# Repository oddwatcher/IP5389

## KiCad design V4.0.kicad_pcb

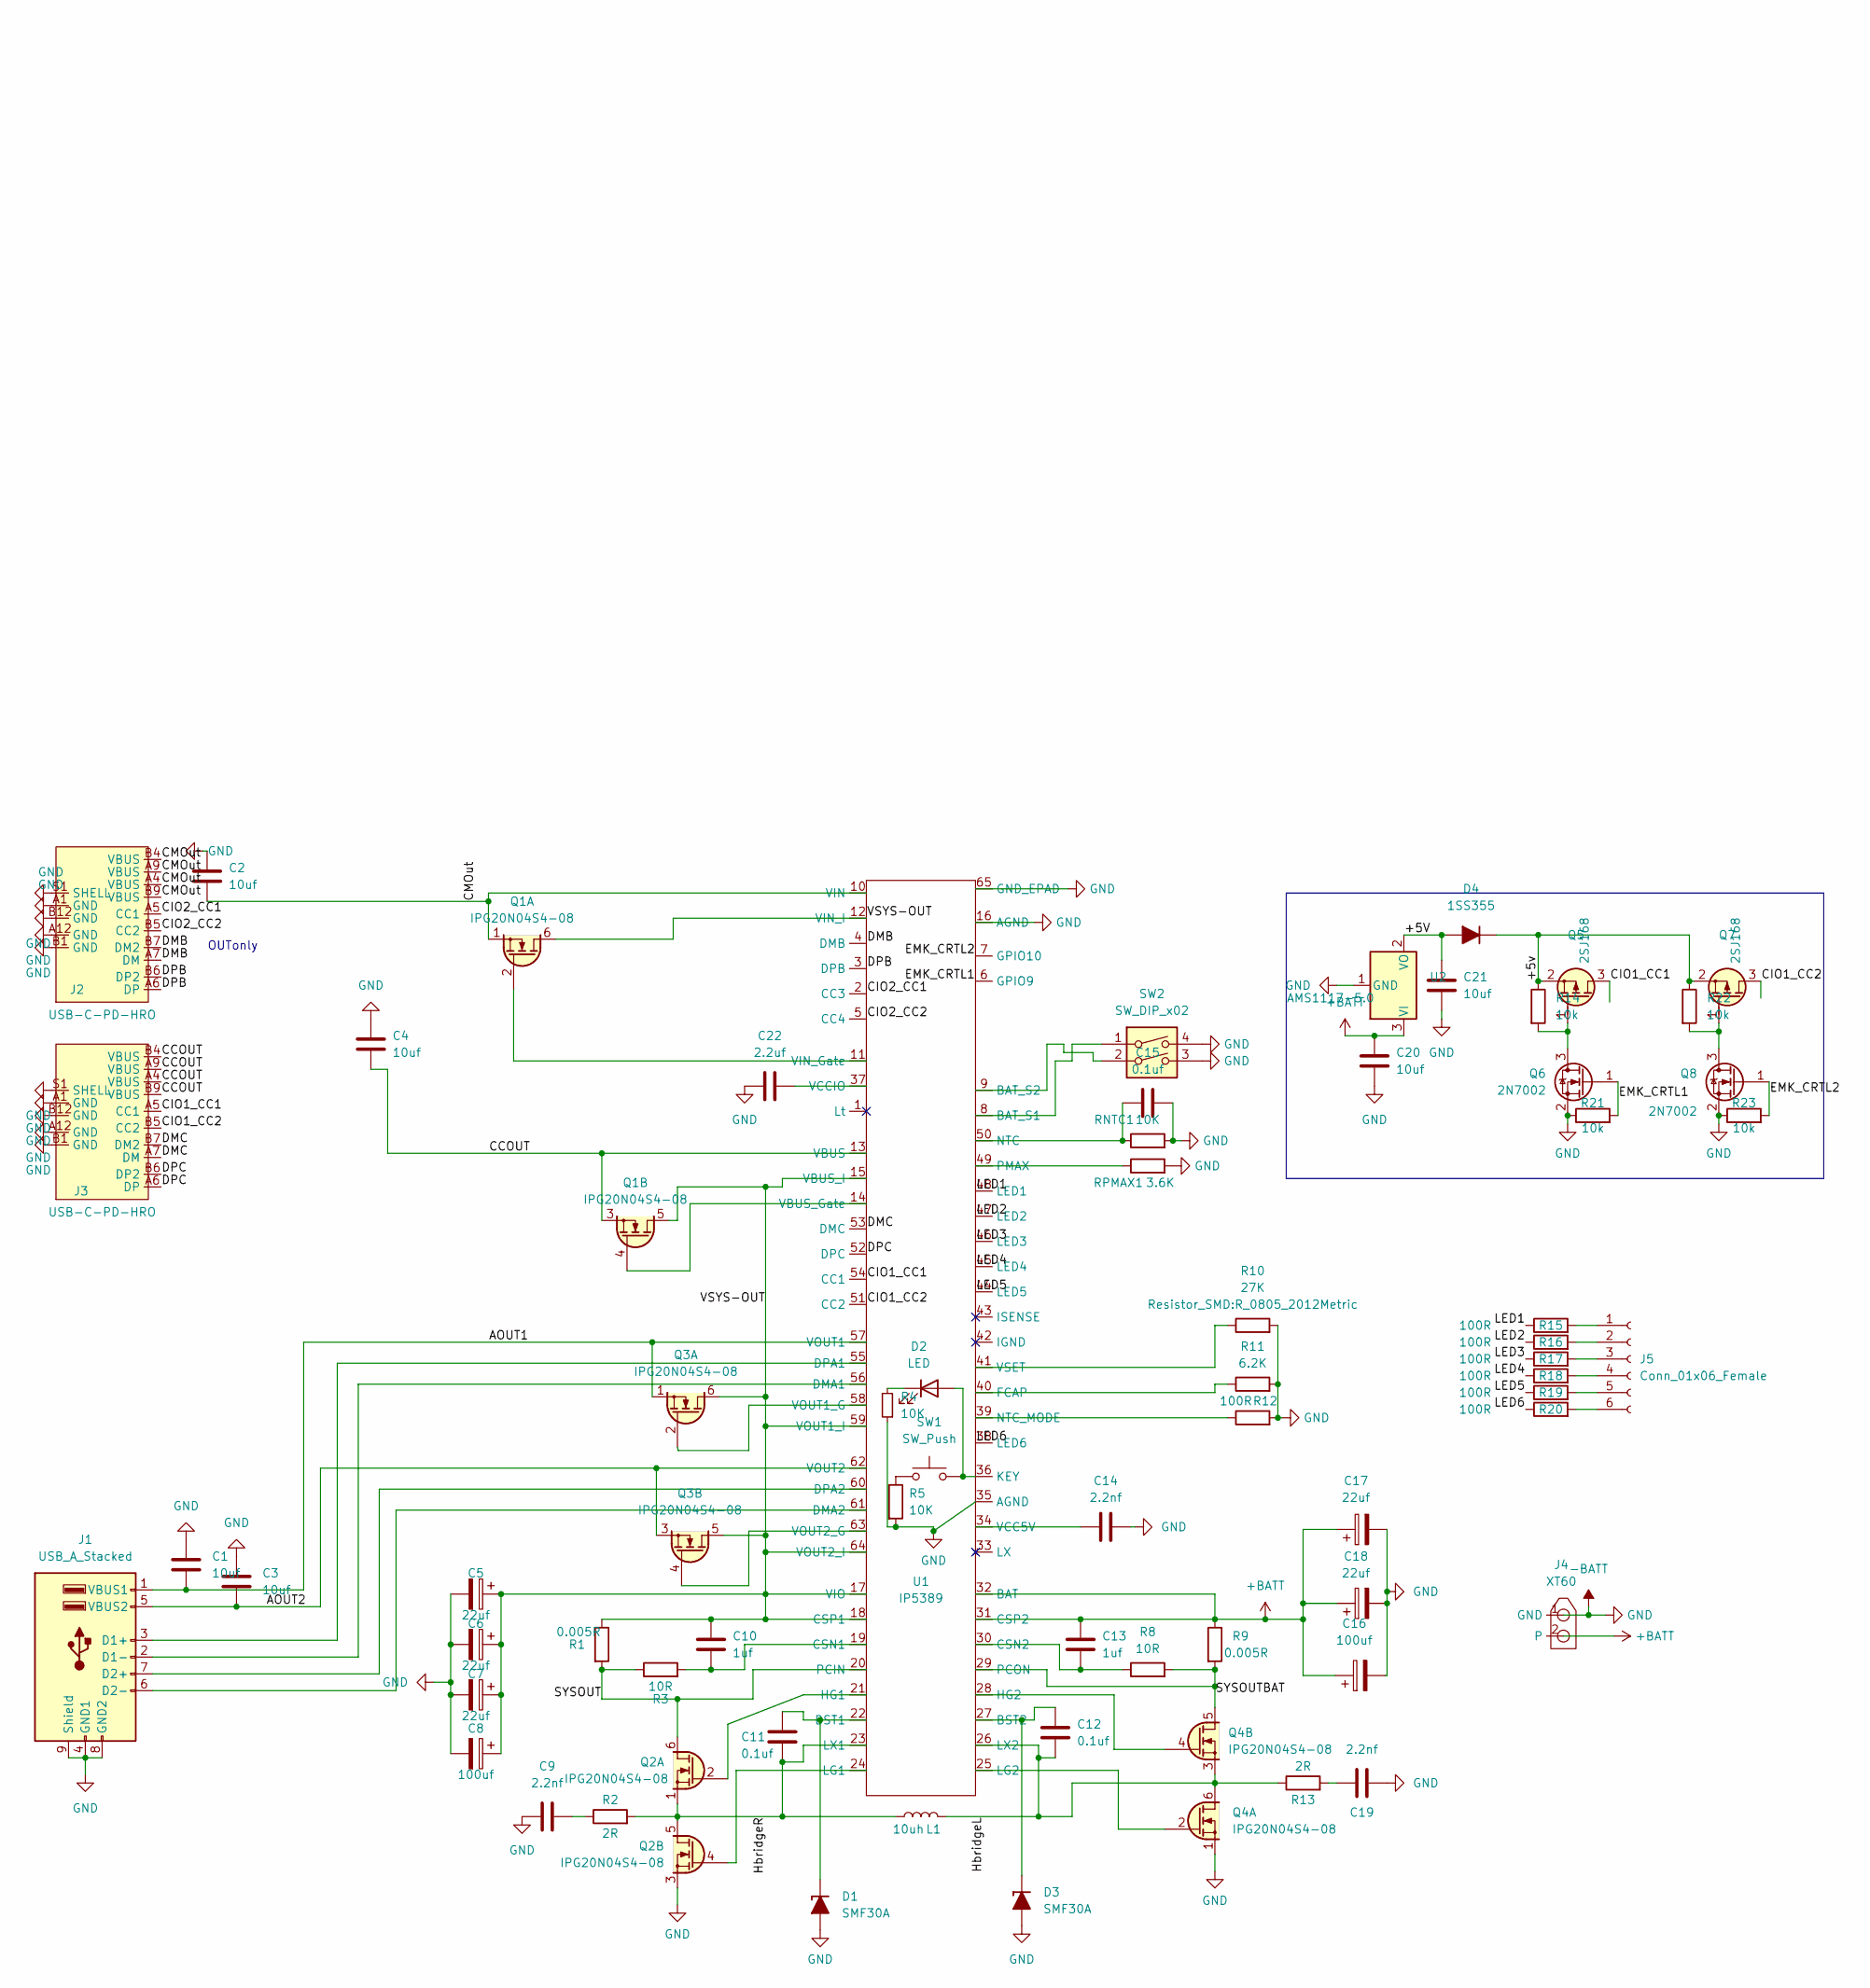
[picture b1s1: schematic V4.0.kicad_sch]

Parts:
C1, C2, C3, C4: 10uf; CP_EIA-7343-31_Kemet-D
C5, C6, C7, C17, C18: 22uf; C_1206_3216Metric
C8, C16: 100uf; CP_EIA-7343-31_Kemet-D
C9, C14, C19: 2.2nf; C_0805_2012Metric
C10, C13: 1uf; C_0805_2012Metric
C11, C12, C15: 0.1uf; C_0805_2012Metric
C20, C21: 10uf; C_0805_2012Metric
C22: 2.2uf; C_0805_2012Metric
D1, D3: SMF30A; D_SOD-123F
D2: LED; C_0805_2012Metric
D4: 1SS355; D_SOD-323
J1: USB_A_Stacked; USB_A_Wuerth_61400826021_Horizontal_Stacked
J2, J3: USB-C-PD-HRO; USB_C_Receptacle_HRO_TYPE-C-31-M-12
J4: XT60; AMASS_XT30U-M_1x02_P5.0mm_Vertical
J5: Conn_01x06_Female; PinHeader_1x06_P2.54mm_Vertical
L1: 10uh; L_12x12mm_H6mm
Q1, Q2, Q3, Q4: IPG20N04S4-08; Infineon_PG-TDSON-8_Dual
Q5, Q7: 2SJ168; SC-59
Q6, Q8: 2N7002; SOT-23
R1, R9: 0.005R; R_1206_3216Metric
R2, R13: 2R; R_1206_3216Metric
R3, R8: 10R; R_0805_2012Metric
R4, R5: 10K; R_0805_2012Metric
R10: 27K; R_0805_2012Metric
R11: 6.2K; R_0805_2012Metric
R12, R15, R16, R17, R18, R19, R20: 100R; R_0805_2012Metric
R14, R21, R22, R23: 10k; R_0805_2012Metric
RNTC1: 10K; R_0805_2012Metric
RPMAX1: 3.6K; R_0805_2012Metric
SW1: SW_Push; SW_Push_1P1T_NO_CK_KMR2
SW2: SW_DIP_x02; SW_DIP_SPSTx02_Slide_6.7x6.64mm_W7.62mm_P2.54mm_LowProfile
U1: IP5389; QFN-64-1EP_8x8mm_P0.4mm_EP6.5x6.5mm_ThermalVias
U2: AMS1117-5.0; SOT-223

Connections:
+BATT: C13.1, C16.1, C17.1, C18.1, C20.1, J4.2, R9.1, U1.31 (CSP2), U1.32 (BAT), U2.3 (VI)
-BATT: C1.1, C2.1, C3.1, C4.1, C5.2, C6.2, C7.2, C8.2, C9.1, C14.2, C15.1, C16.2, C17.2, C18.2, C19.1, C20.2, C21.2, C22.1, D1.2 (A), D3.2 (A), J1.4 (GND1), J1.8 (GND2), J1.9 (Shield), J2.A1 (GND), J2.A12 (GND), J2.B1 (GND), J2.B12 (GND), J2.S1 (SHELL), J3.A1 (GND), J3.A12 (GND), J3.B1 (GND), J3.B12 (GND), J3.S1 (SHELL), J4.1 (GND), Q2.3 (S2), Q4.1 (S1), Q6.2 (S), Q8.2 (S), R4.1, R5.2, R10.2, R11.2, R12.2, R21.1, R23.1, RNTC1.2, RPMAX1.2, SW2.3, SW2.4, U1.16 (AGND), U1.35 (AGND), U1.65 (GND_EPAD), U2.1 (GND)
/+5V: C21.1, D4.2 (A), U2.2 (VO)
/+5v: D4.1 (K), Q5.2 (S), Q7.2 (S), R14.1, R22.1
/AOUT1: C1.2, J1.1 (VBUS1), Q3.1 (S1), U1.57 (VOUT1)
/AOUT2: C3.2, J1.5 (VBUS2), Q3.3 (S2), U1.62 (VOUT2)
/CCOUT: C4.2, J3.A4 (VBUS), J3.A9 (VBUS), J3.B4 (VBUS), J3.B9 (VBUS), Q1.3 (S2), U1.13 (VBUS)
/CIO1_CC1: J3.A5 (CC1), Q5.3 (D), U1.54 (CC1)
/CIO1_CC2: J3.B5 (CC2), Q7.3 (D), U1.51 (CC2)
/CIO2_CC1: J2.A5 (CC1), U1.2 (CC3)
/CIO2_CC2: J2.B5 (CC2), U1.5 (CC4)
/CMOut: C2.2, J2.A4 (VBUS), J2.A9 (VBUS), J2.B4 (VBUS), J2.B9 (VBUS), Q1.1 (S1), U1.10 (VIN)
/DMB: J2.A7 (DM), J2.B7 (DM2), U1.4 (DMB)
/DMC: J3.A7 (DM), J3.B7 (DM2), U1.53 (DMC)
/DPB: J2.A6 (DP), J2.B6 (DP2), U1.3 (DPB)
/DPC: J3.A6 (DP), J3.B6 (DP2), U1.52 (DPC)
/EMK_CRTL1: Q6.1 (G), R21.2, U1.6 (GPIO9)
/EMK_CRTL2: Q8.1 (G), R23.2, U1.7 (GPIO10)
/HbridgeL: C12.2, L1.2, Q4.3 (S2), Q4.6 (D1), R13.1, U1.26 (LX2)
/HbridgeR: C11.2, L1.1, Q2.1 (S1), Q2.5 (D2), R2.2, U1.23 (LX1)
/LED1: R15.1, U1.48 (LED1)
/LED2: R16.1, U1.47 (LED2)
/LED3: R17.1, U1.46 (LED3)
/LED4: R18.1, U1.45 (LED4)
/LED5: R19.1, U1.44 (LED5)
/LED6: R20.1, U1.38 (LED6)
/SYSOUT: Q2.6 (D1), R1.2, R3.1, U1.20 (PCIN)
/SYSOUTBAT: Q4.5 (D2), R8.2, R9.2, U1.29 (PCON)
/VSYS-OUT: C5.1, C6.1, C7.1, C8.1, C10.1, Q1.5 (D2), Q1.6 (D1), Q3.5 (D2), Q3.6 (D1), R1.1, U1.12 (VIN_I), U1.15 (VBUS_I), U1.17 (VIO), U1.18 (CSP1), U1.59 (VOUT1_I), U1.64 (VOUT2_I)
unnamed: C9.2, R2.1
unnamed: C10.2, R3.2, U1.19 (CSN1)
unnamed: C11.1, D1.1 (K), U1.22 (BST1)
unnamed: C12.1, D3.1 (K), U1.27 (BST2)
unnamed: C13.2, R8.1, U1.30 (CSN2)
unnamed: C14.1, U1.34 (VCC5V)
unnamed: C15.2, RNTC1.1, U1.50 (NTC)
unnamed: C19.2, R13.2
unnamed: C22.2, U1.37 (VCCIO)
unnamed: D2.1 (K), R4.2
unnamed: D2.2 (A), SW1.2, U1.36 (KEY)
unnamed: J1.2 (D1-), U1.56 (DMA1)
unnamed: J1.3 (D1+), U1.55 (DPA1)
unnamed: J1.6 (D2-), U1.61 (DMA2)
unnamed: J1.7 (D2+), U1.60 (DPA2)
unnamed: J5.1, R15.2
unnamed: J5.2, R16.2
unnamed: J5.3, R17.2
unnamed: J5.4, R18.2
unnamed: J5.5, R19.2
unnamed: J5.6, R20.2
unnamed: Q1.2 (G1), U1.11 (VIN_Gate)
unnamed: Q1.4 (G2), U1.14 (VBUS_Gate)
unnamed: Q2.2 (G1), U1.21 (HG1)
unnamed: Q2.4 (G2), U1.24 (LG1)
unnamed: Q3.2 (G1), U1.58 (VOUT1_G)
unnamed: Q3.4 (G2), U1.63 (VOUT2_G)
unnamed: Q4.2 (G1), U1.25 (LG2)
unnamed: Q4.4 (G2), U1.28 (HG2)
unnamed: Q5.1 (G), Q6.3 (D), R14.2
unnamed: Q7.1 (G), Q8.3 (D), R22.2
unnamed: R5.1, SW1.1
unnamed: R10.1, U1.41 (VSET)
unnamed: R11.1, U1.40 (FCAP)
unnamed: R12.1, U1.39 (NTC_MODE)
unnamed: RPMAX1.1, U1.49 (PMAX)
unnamed: SW2.1, U1.8 (BAT_S1)
unnamed: SW2.2, U1.9 (BAT_S2)

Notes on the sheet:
OUTonly

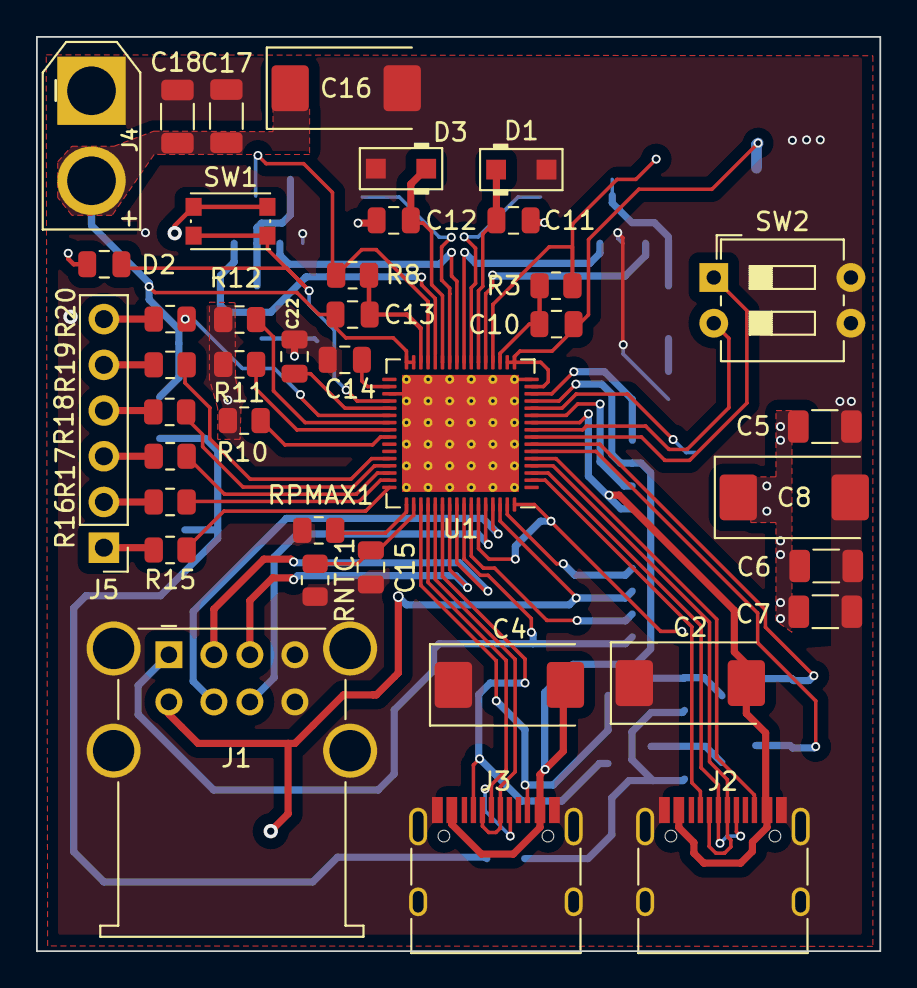
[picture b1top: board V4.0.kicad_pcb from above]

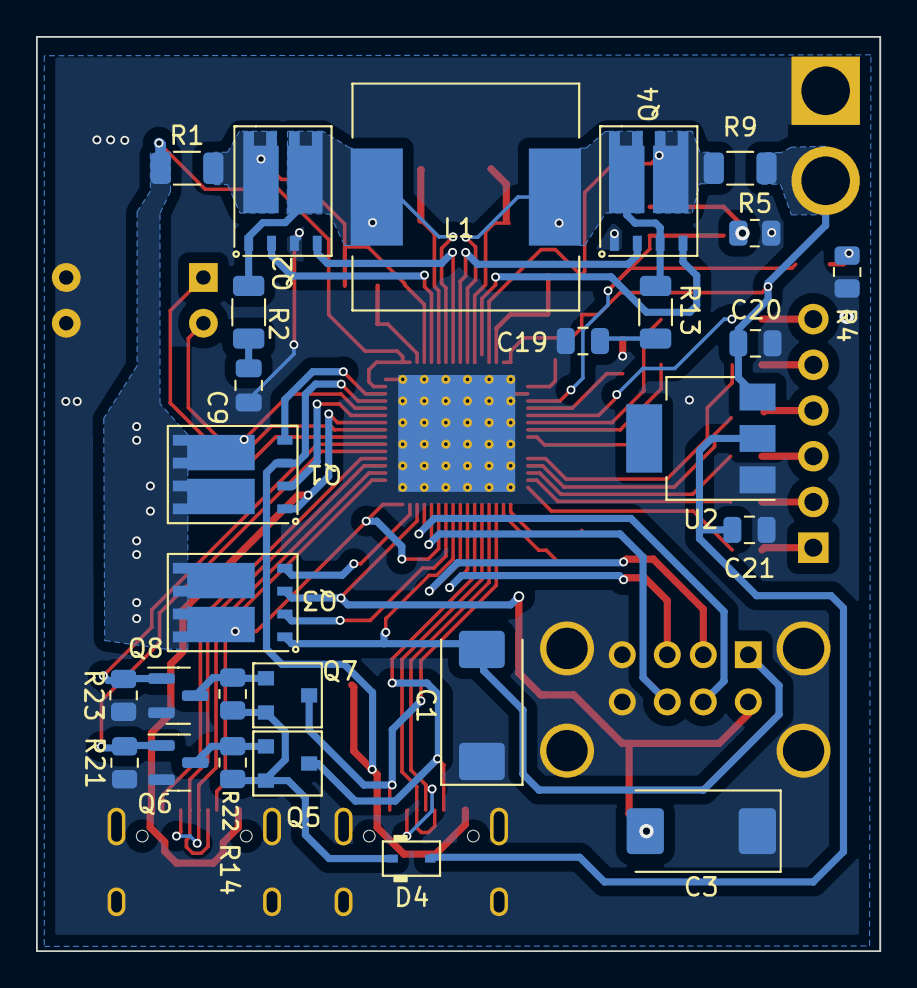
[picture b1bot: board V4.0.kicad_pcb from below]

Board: 2 copper layers, 46.9 x 50.8 mm, 67 parts (27 on the bottom side), 67 nets.

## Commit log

2022-06-14 first
2022-06-23 fixed parameter
